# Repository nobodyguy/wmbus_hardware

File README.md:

# WM-bus to USB board
* KiCAD 6.X required 
* iM871A module
* includes USB ESD protection
* includes CH340E UART IC

## Software
Tested with https://github.com/weetmuts/wmbusmeters library.

## Board overview

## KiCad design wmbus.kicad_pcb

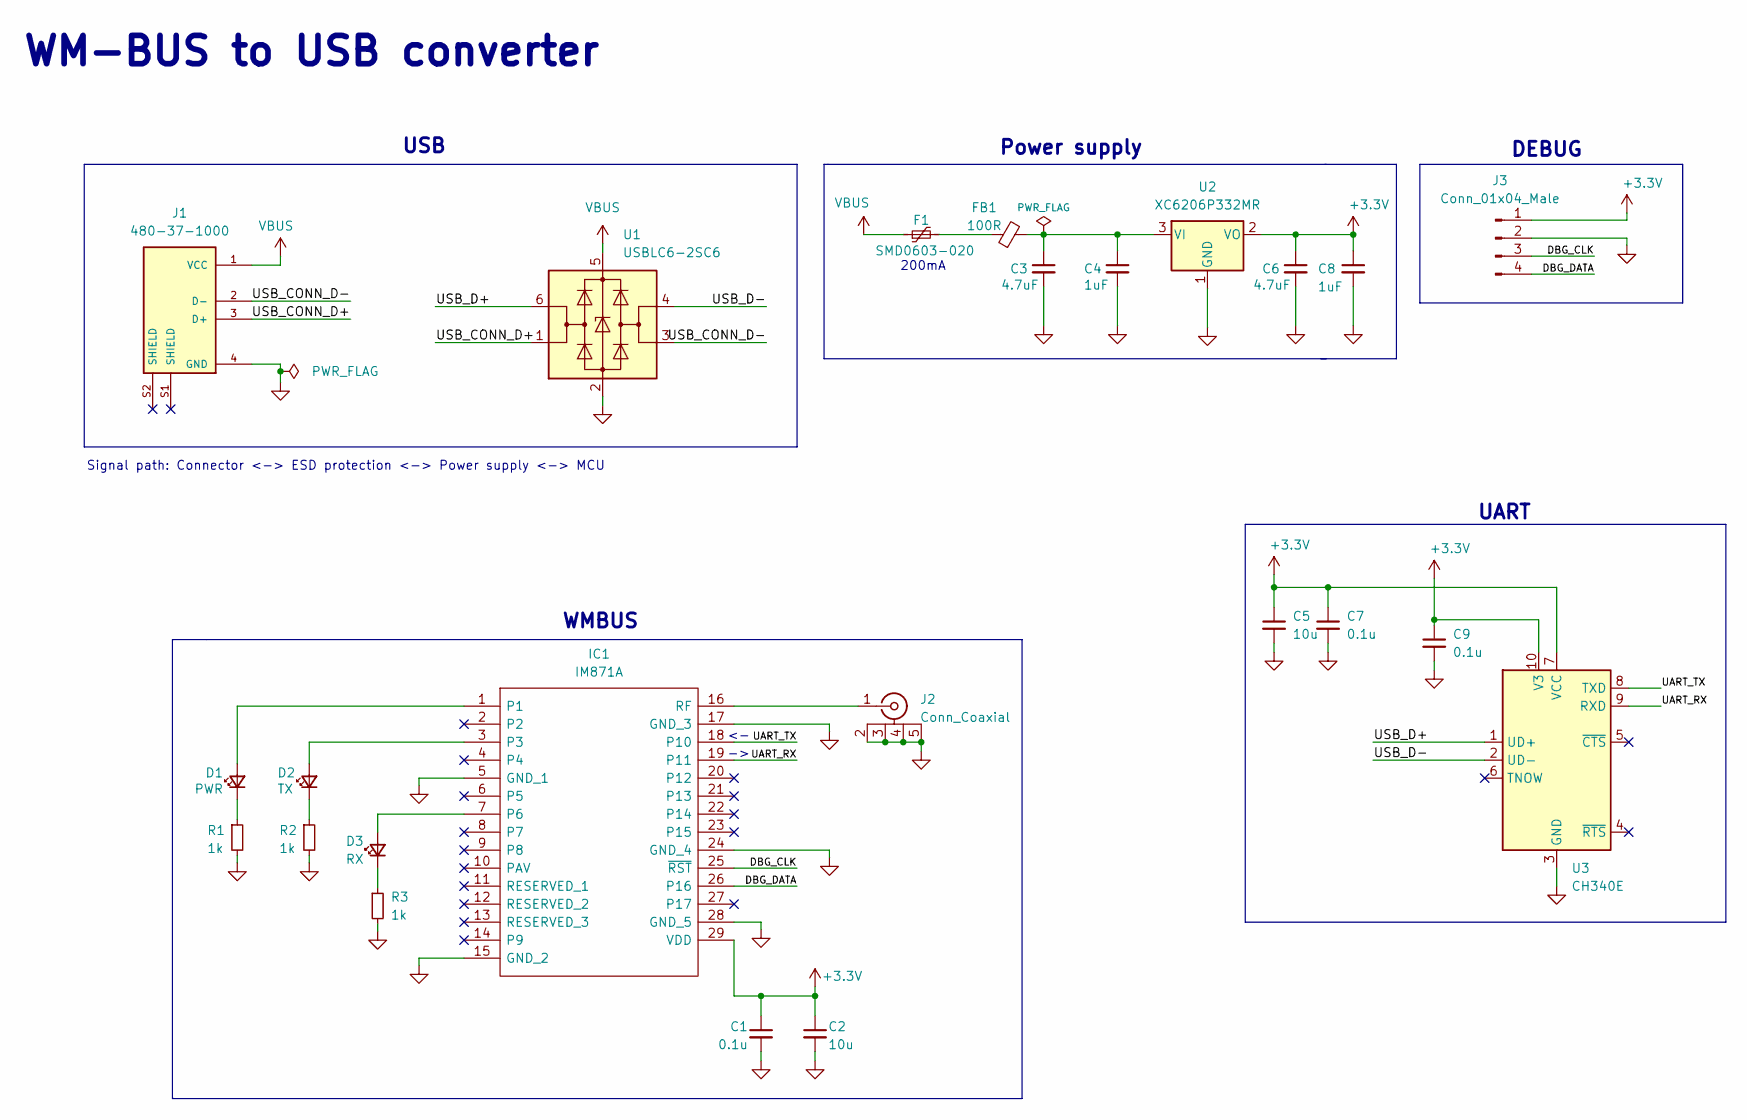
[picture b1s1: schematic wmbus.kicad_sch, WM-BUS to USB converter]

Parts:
C1, C7, C9: 0.1u; C_0603_1608Metric; LCSC Part C14663
C2, C5: 10u; C_0603_1608Metric; LCSC Part C109455
C3, C6: 4.7uF; C_0603_1608Metric; LCSC Part C1592
C4, C8: 1uF; C_0603_1608Metric; LCSC Part C1592
D1: PWR; D_0603_1608Metric; LCSC Part C72043
D2: TX; D_0603_1608Metric; LCSC Part C72043
D3: RX; D_0603_1608Metric; LCSC Part C72043
F1: SMD0603-020; Fuse_0603_1608Metric; LCSC Part C2760255
FB1: 100R; L_0603_1608Metric; LCSC Part C74325
IC1: IM871A; Manufacturer_Part_Number IM871A
J1: 480-37-1000; MOLEX_480-37-1000; PARTREV D
J2: Conn_Coaxial; SMA-SMD_BWSMA-KE-P001
J3: Conn_01x04_Male; PinHeader_1x04_P2.54mm_Vertical
R1, R2, R3: 1k; R_0603_1608Metric; LCSC Part C22548
U1: USBLC6-2SC6; SOT-23-6; LCSC Part C2827654
U2: XC6206P332MR; SOT-23; LCSC Part C5446
U3: CH340E; MSOP-10_3x3mm_P0.5mm; LCSC Part C99652

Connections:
+3.3V: C1.1, C2.1, C5.1, C6.1, C7.1, C8.1, C9.1, IC1.29 (VDD), J3.1, U2.2 (VO), U3.7 (VCC), U3.10 (V3)
/DBG_CLK: IC1.25 (~RST), J3.3
/DBG_DATA: IC1.26 (P16), J3.4
/UART_RX: IC1.19 (P11), U3.9 (RXD)
/UART_TX: IC1.18 (P10), U3.8 (TXD)
/USB_CONN_D+: J1.3 (D+), U1.1 (I/O1)
/USB_CONN_D-: J1.2 (D-), U1.3 (I/O2)
/USB_D+: U1.6 (I/O1), U3.1 (UD+)
/USB_D-: U1.4 (I/O2), U3.2 (UD-)
GND: C1.2, C2.2, C3.2, C4.2, C5.2, C6.2, C7.2, C8.2, C9.2, IC1.5 (GND_1), IC1.15 (GND_2), IC1.17 (GND_3), IC1.24 (GND_4), IC1.28 (GND_5), J1.4 (GND), J2.2 (Ext), J2.3 (Ext), J2.4 (Ext), J2.5 (Ext), J3.2, R1.2, R2.2, R3.2, U1.2 (GND), U2.1 (GND), U3.3 (GND)
unnamed: C3.1, C4.1, FB1.2, U2.3 (VI)
unnamed: D1.1 (K), R1.1
unnamed: D1.2 (A), IC1.1
unnamed: D2.1 (K), R2.1
unnamed: D2.2 (A), IC1.3
unnamed: D3.1 (K), R3.1
unnamed: D3.2 (A), IC1.7 (P6)
unnamed: F1.2, FB1.1
unnamed: IC1.16 (RF), J2.1 (In)
VBUS: F1.1, J1.1 (VCC), U1.5 (VBUS)

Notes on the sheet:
200mA
UART
WMBUS
DEBUG
Signal path: Connector <-> ESD protection <-> Power supply <-> MCU
USB
Power supply
WM-BUS to USB converter

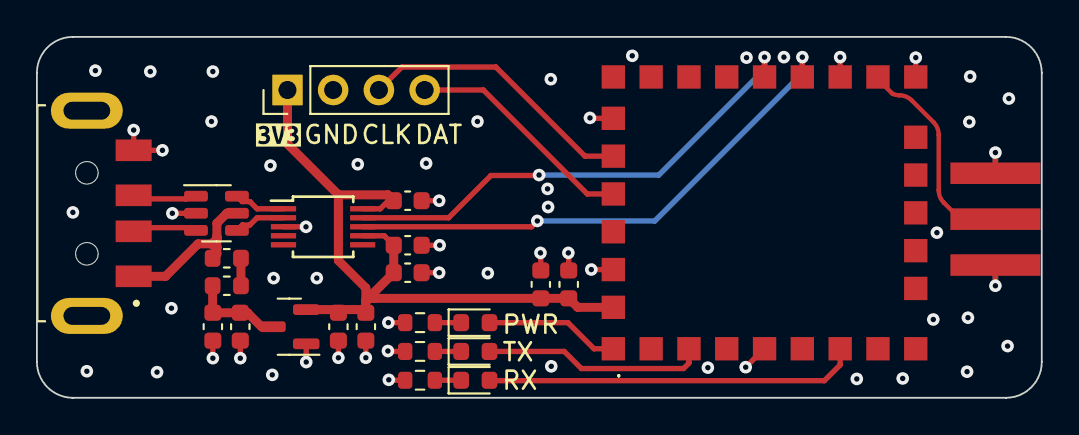
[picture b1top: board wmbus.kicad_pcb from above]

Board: 4 copper layers, 55.8 x 20.0 mm, 26 parts (1 on the bottom side), 20 nets.

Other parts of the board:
kibuzzard-636EC376: G***; kibuzzard-636EC376
kibuzzard-6361777F: G***; kibuzzard-6361777F

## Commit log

2022-11-03 Initial version without routing
2022-11-03 Routing done
2022-11-04 Ready for production rev1
2022-11-06 Added antenna 3D model, removed useless GND via, unified via size
2022-11-06 Updated SMA connector 3D model
2022-11-06 Added renders to readme
2022-11-16 Added more info to readme
2022-12-02 Rounded RF track
2022-12-02 rev2 - smaller, removed unused rx/tx jumpers
2022-12-02 Added 3D printed box
2023-02-17 Added photo of real boards
